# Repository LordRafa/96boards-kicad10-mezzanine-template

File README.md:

96boards Mezzanine Project Template

MEZZANINE PROJECT TEMPLATE
===============================================

This project provides you with all the base files required for 
a mezzanine pcb project.

#### What is this project for?

This is a project template for anyone who wants to develop a 96Boards
Mezzanine board <a
href="https://www.96boards.org/products/ce/">(compatible with these
boards)</a>.

This project's schematic only contains the necessary connectors needed
for a mezzanine board. By default it is set up for SMD connectors, but
can easily be changed to through-hole.

The <em>PCB</em> includes the connectors and mounting holes. The holes
and connectors have been positioned so that the boards are aligned when
mounted. The <em>edge cuts</em> also aligns with the base board. All the
mezzanine board low-speed expansion connector <em>IO</em> is connected
to the header pins.

#### How to use this project

This project has been formatted to work with KiCad's "New Project from
Template" tool. You should clone this project into your KiCad templates
directory. For example, on OSX the system template directory is
<em>/Library/Application Support/kicad/template/</em>. A Linux user's
template directory is <em>$HOME/kicad/template/</em>

Once cloned, you can use the new template by navigating to
File > New Project > New Project From Template. After selecting your
save location, click on <em>System Templates</em> or <em>User
Templates</em> (depending on which file path you previously selected to
clone the project to). Upon validation of the file path, the 96Boards
mezzanine template should appear under the 96Boards logo. Select the
template and you'll be good to go.

##### Changing to Through Hole Connector
By default, this project loads with the connectors set up as SMD. If you
would prefer to use a through hole instead, follow the instructions on
the schematic to delete a connector and change the footprint on the
other. To change the footprint, right click and select <em>Edit
Component</em>. In the dialog box, click on the footprint section, then
on the right there should now be a button called <em>Assign
Footprint</em>. Click the button, and choose the different footprint
file. Create a new netlist file, open up the PCB editor, and <em>Load
Netlist</em>, ensuring that <em>Exchange Footprint</em> is set to
CHANGE, and <em>Extra Footprints</em> is set to DELETE. Click <em>Read
Current Netlist</em> to load the new connector. Now you should have only
one connector on the board, and when you view in 3D view, there will be
a through hole connector.

Copyright (c) 2016, Linaro, Inc.

Copyright (c) 2026, Rafael Waldo

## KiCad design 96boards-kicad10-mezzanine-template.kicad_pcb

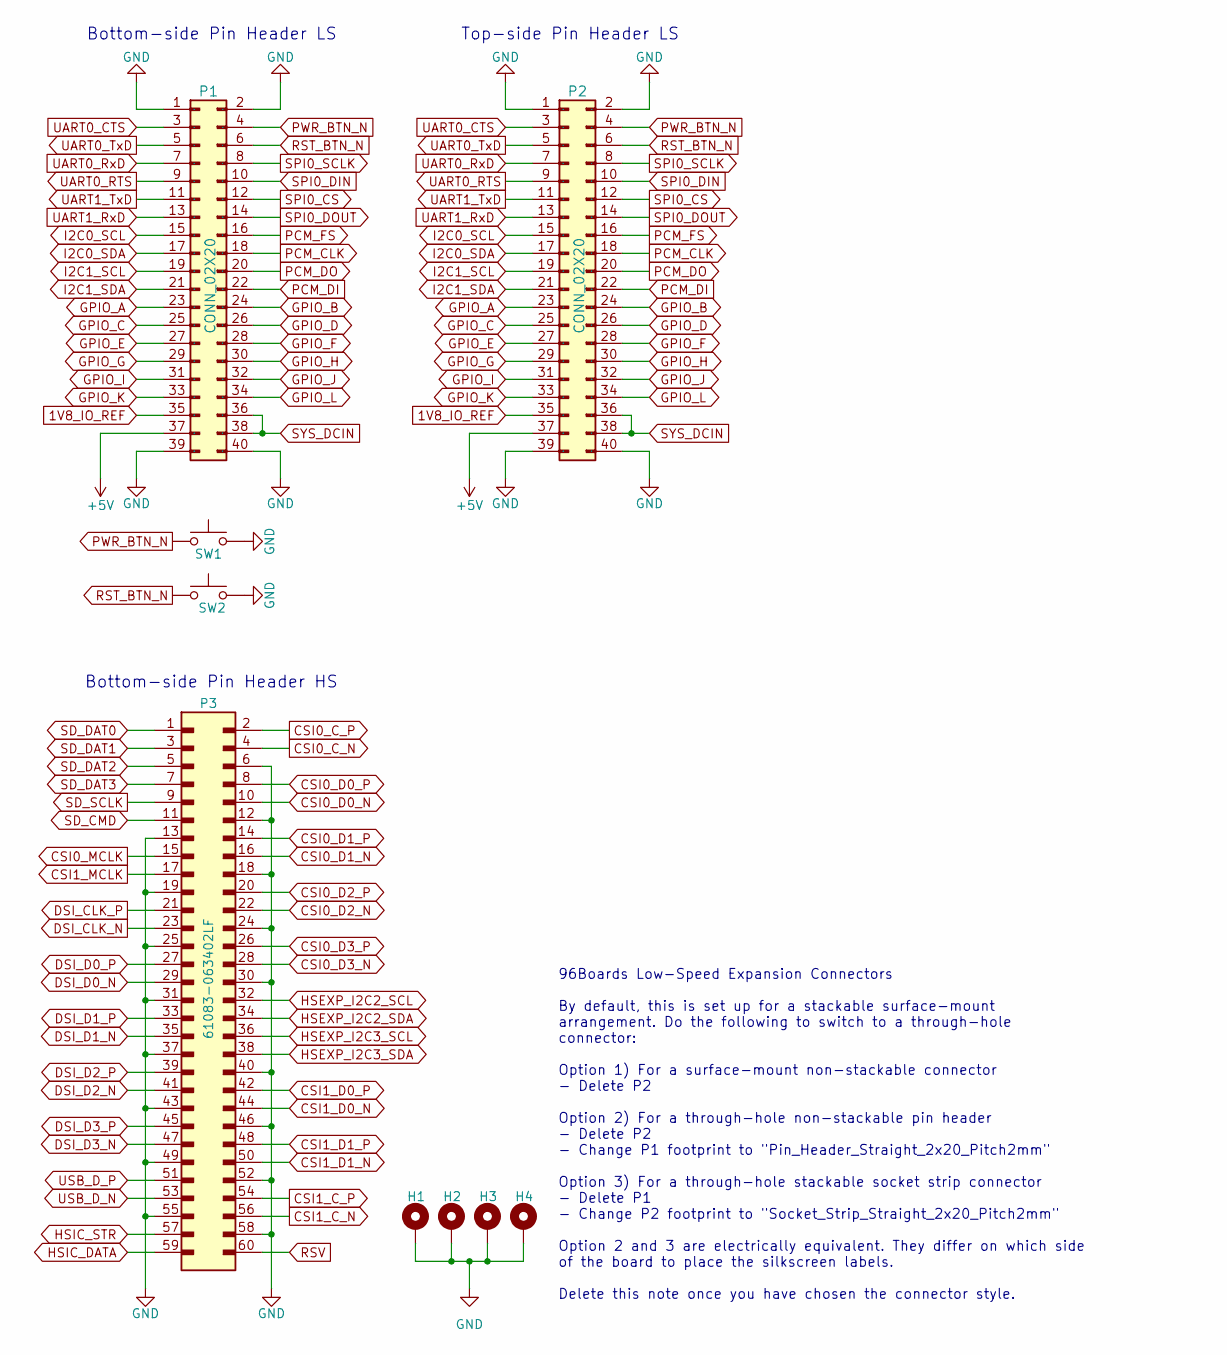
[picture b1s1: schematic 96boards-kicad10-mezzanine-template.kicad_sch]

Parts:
H1, H2, H3, H4: MountingHole_Pad; Hole_2.5MM
P1: CONN_02X20; Pin_Header_SMD_2x20_Pitch2mm
P2: CONN_02X20; Socket_Strip_SMD_2x20_Pitch2mm
P3: 61083-063402LF; AMPHENOL_61083-063402LF; PARTREV AT
SW1, SW2: SW_Push; SW_Push_1P1T_NO_CK_KMR2

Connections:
1V8_IO_REF: P1.35, P2.35
+5V: P1.37, P2.37
CSI0_C_N: P3.4
CSI0_C_P: P3.2
CSI0_D0_N: P3.10
CSI0_D0_P: P3.8
CSI0_D1_N: P3.16
CSI0_D1_P: P3.14
CSI0_D2_N: P3.22
CSI0_D2_P: P3.20
CSI0_D3_N: P3.28
CSI0_D3_P: P3.26
CSI0_MCLK: P3.15
CSI1_C_N: P3.56
CSI1_C_P: P3.54
CSI1_D0_N: P3.44
CSI1_D0_P: P3.42
CSI1_D1_N: P3.50
CSI1_D1_P: P3.48
CSI1_MCLK: P3.17
DSI_CLK_N: P3.23
DSI_CLK_P: P3.21
DSI_D0_N: P3.29
DSI_D0_P: P3.27
DSI_D1_N: P3.35
DSI_D1_P: P3.33
DSI_D2_N: P3.41
DSI_D2_P: P3.39
DSI_D3_N: P3.47
DSI_D3_P: P3.45
GND: H1.1 (1_1), H2.1 (1_1), H3.1 (1_1), H4.1 (1_1), P1.1, P1.2, P1.39, P1.40, P2.1, P2.2, P2.39, P2.40, P3.6, P3.12, P3.13, P3.18, P3.19, P3.24, P3.25, P3.30, P3.31, P3.37, P3.40, P3.43, P3.46, P3.49, P3.52, P3.55, P3.58, SW1.1, SW2.1
GPIO_A: P1.23, P2.23
GPIO_B: P1.24, P2.24
GPIO_C: P1.25, P2.25
GPIO_D: P1.26, P2.26
GPIO_E: P1.27, P2.27
GPIO_F: P1.28, P2.28
GPIO_G: P1.29, P2.29
GPIO_H: P1.30, P2.30
GPIO_I: P1.31, P2.31
GPIO_J: P1.32, P2.32
GPIO_K: P1.33, P2.33
GPIO_L: P1.34, P2.34
HSEXP_I2C2_SCL: P3.32
HSEXP_I2C2_SDA: P3.34
HSEXP_I2C3_SCL: P3.36
HSEXP_I2C3_SDA: P3.38
HSIC_DATA: P3.59
HSIC_STR: P3.57
I2C0_SCL: P1.15, P2.15
I2C0_SDA: P1.17, P2.17
I2C1_SCL: P1.19, P2.19
I2C1_SDA: P1.21, P2.21
PCM_CLK: P1.18, P2.18
PCM_DI: P1.22, P2.22
PCM_DO: P1.20, P2.20
PCM_FS: P1.16, P2.16
PWR_BTN_N: P1.4, P2.4, SW1.2
RST_BTN_N: P1.6, P2.6, SW2.2
RSV: P3.60
SD_CMD: P3.11
SD_DAT0: P3.1
SD_DAT1: P3.3
SD_DAT2: P3.5
SD_DAT3: P3.7
SD_SCLK: P3.9
SPI0_CS: P1.12, P2.12
SPI0_DIN: P1.10, P2.10
SPI0_DOUT: P1.14, P2.14
SPI0_SCLK: P1.8, P2.8
SYS_DCIN: P1.36, P1.38, P2.36, P2.38
UART0_CTS: P1.3, P2.3
UART0_RTS: P1.9, P2.9
UART0_RxD: P1.7, P2.7
UART0_TxD: P1.5, P2.5
UART1_RxD: P1.13, P2.13
UART1_TxD: P1.11, P2.11
USB_D_N: P3.53
USB_D_P: P3.51

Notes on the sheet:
96Boards Low-Speed Expansion Connectors By default, this is set up for a stackable surface-mount arrangement. Do the following to switch to a through-hole connector: Option 1) For a surface-mount non-stackable connector - Delete P2 Option 2) For a through-hole non-stackable pin header - Delete P2 -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
Top-side Pin Header LS
Bottom-side Pin Header LS
Bottom-side Pin Header HS

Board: 2 copper layers, 9 parts (2 on the bottom side), 36 nets, no tracks yet.

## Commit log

2026-04-17 Initial code base
2026-04-17 Removing missing library
